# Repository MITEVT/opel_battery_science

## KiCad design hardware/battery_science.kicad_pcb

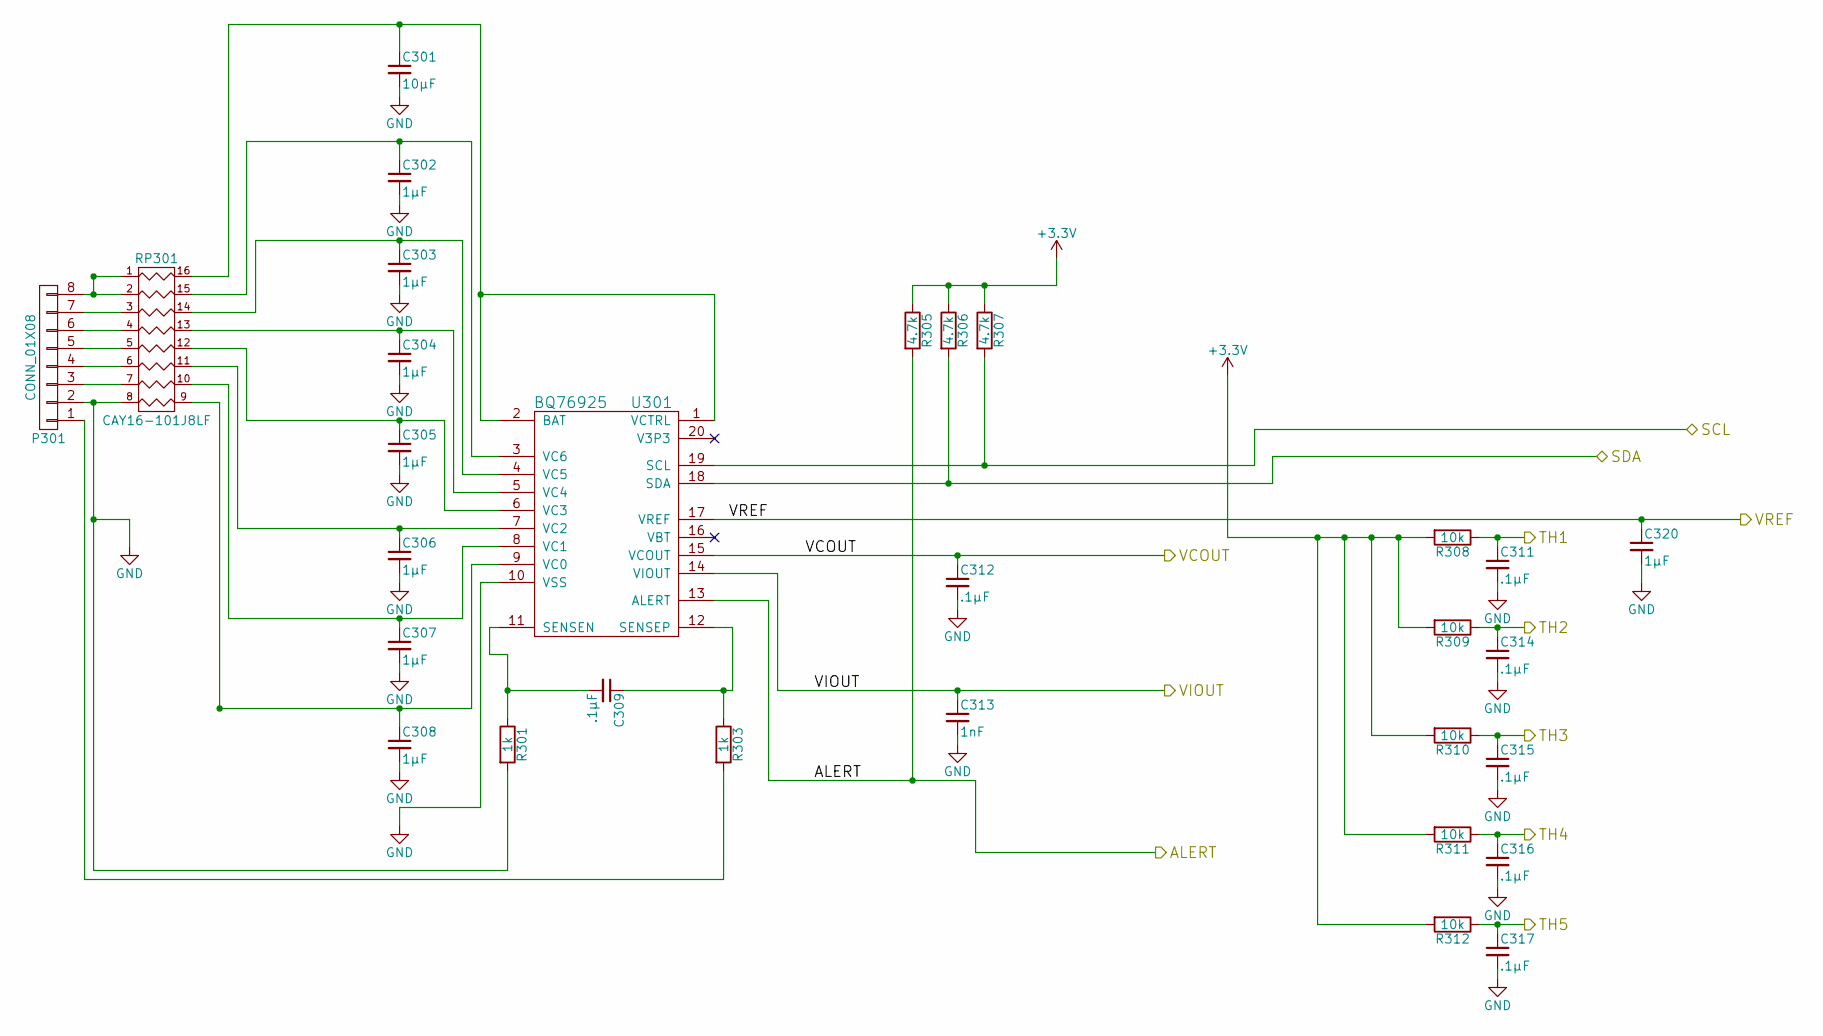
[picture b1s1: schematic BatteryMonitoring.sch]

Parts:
C301: 10μF; C_0603_HandSoldering
C302, C303, C304, C305, C306, C307, C308, C320: 1μF; C_0603_HandSoldering
C309, C311, C312, C314, C315, C316, C317: .1μF; C_0603_HandSoldering
C313: 1nF; C_0603_HandSoldering
P301: CONN_01X08; Pin_Header_Straight_1x08
R301, R303: 1k; R_0603_HandSoldering
R305, R306, R307: 4.7k; R_0603_HandSoldering
R308, R309, R310, R311, R312: 10k; R_0603_HandSoldering
RP301: CAY16-101J8LF; R_Cat16-8
U301: BQ76925; TSSOP-20_4.4x6.5mm_Pitch0.65mm

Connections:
+3V3: R305.1, R306.1, R307.1, R308.2, R309.2, R310.2, R311.2, R312.2; also elsewhere on the board
/ADC/Thermistors/TH1: C311.1, R308.1; also elsewhere on the board
/ADC/Thermistors/TH2: C314.1, R309.1; also elsewhere on the board
/ADC/Thermistors/TH3: C315.1, R310.1; also elsewhere on the board
/ADC/Thermistors/TH4: C316.1, R311.1; also elsewhere on the board
/ADC/Thermistors/TH5: C317.1, R312.1; also elsewhere on the board
/ADC/Thermistors/VCOUT: C312.1, U301.15 (VCOUT); also elsewhere on the board
/ADC/Thermistors/VIOUT: C313.1, U301.14 (VIOUT); also elsewhere on the board
/ADC/Thermistors/VREF: C320.1, U301.17 (VREF); also elsewhere on the board
/BatteryMonitoring/ALERT: R305.2, U301.13 (ALERT); also elsewhere on the board
/BatteryMonitoring/SCL: R307.2, U301.19 (SCL); also elsewhere on the board
/BatteryMonitoring/SDA: R306.2, U301.18 (SDA); also elsewhere on the board
GND: C301.2, C302.2, C303.2, C304.2, C305.2, C306.2, C307.2, C308.2, C311.2, C312.2, C313.2, C314.2, C315.2, C316.2, C317.2, C320.2, P301.2, R301.2, RP301.8, U301.10 (VSS); also elsewhere on the board
unnamed: C301.1, RP301.16 (R1), U301.1 (VCTRL), U301.2 (BAT)
unnamed: C302.1, RP301.15 (R2), U301.3 (VC6)
unnamed: C303.1, RP301.14 (R3), U301.4 (VC5)
unnamed: C304.1, RP301.13 (R4), U301.5 (VC4)
unnamed: C305.1, RP301.12 (R5), U301.6 (VC3)
unnamed: C306.1, RP301.11 (R6), U301.7 (VC2)
unnamed: C307.1, RP301.10 (R7), U301.8 (VC1)
unnamed: C308.1, RP301.9 (R8), U301.9 (VC0)
unnamed: C309.1, R303.1, U301.12 (SENSEP)
unnamed: C309.2, R301.1, U301.11 (SENSEN)
unnamed: P301.1, R303.2
unnamed: P301.3, RP301.7
unnamed: P301.4, RP301.6
unnamed: P301.5, RP301.5
unnamed: P301.6, RP301.4
unnamed: P301.7, RP301.3
unnamed: P301.8, RP301.1, RP301.2

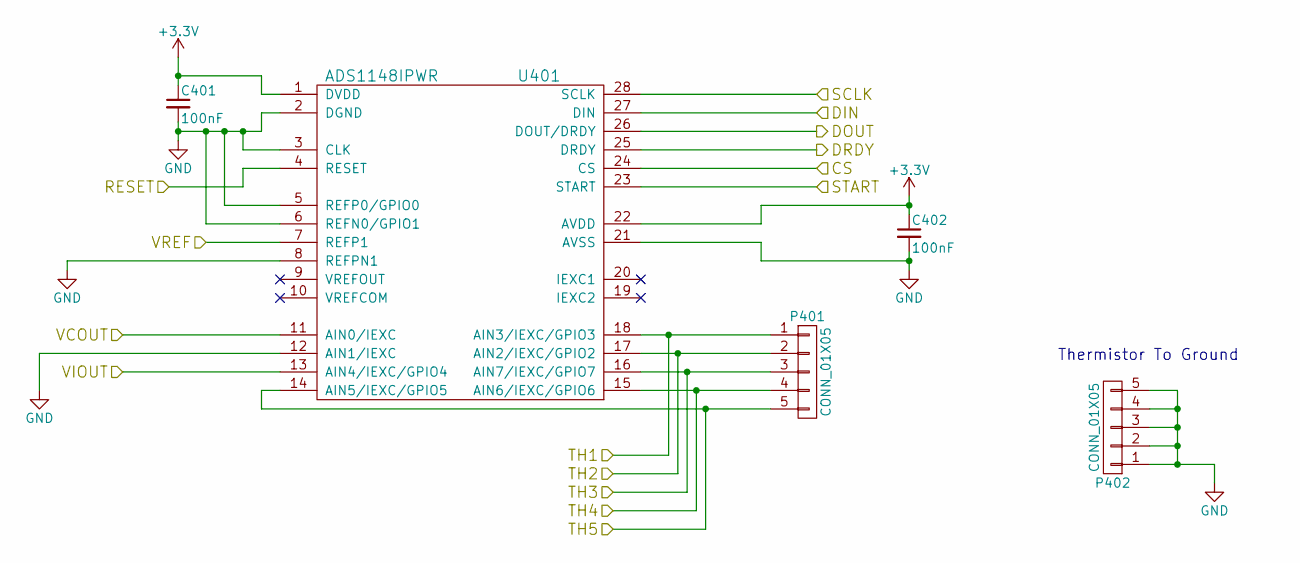
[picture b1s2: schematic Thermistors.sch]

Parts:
C401, C402: 100nF; C_0603_HandSoldering
P401, P402: CONN_01X05; Pin_Header_Straight_1x05
U401: ADS1148IPWR; TSSOP-28_4.4x9.7mm_Pitch0.65mm

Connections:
+3V3: C401.1, C402.1, U401.1 (DVDD), U401.22 (AVDD); also elsewhere on the board
/ADC/Thermistors/CS: U401.24 (CS); also elsewhere on the board
/ADC/Thermistors/DIN: U401.27 (DIN); also elsewhere on the board
/ADC/Thermistors/DOUT: U401.26 (DOUT/DRDY); also elsewhere on the board
/ADC/Thermistors/DRDY: U401.25 (DRDY); also elsewhere on the board
/ADC/Thermistors/RESET: U401.4 (RESET); also elsewhere on the board
/ADC/Thermistors/SCLK: U401.28 (SCLK); also elsewhere on the board
/ADC/Thermistors/START: U401.23 (START); also elsewhere on the board
/ADC/Thermistors/TH1: P401.1, U401.18 (AIN3/IEXC/GPIO3); also elsewhere on the board
/ADC/Thermistors/TH2: P401.2, U401.17 (AIN2/IEXC/GPIO2); also elsewhere on the board
/ADC/Thermistors/TH3: P401.3, U401.16 (AIN7/IEXC/GPIO7); also elsewhere on the board
/ADC/Thermistors/TH4: P401.4, U401.15 (AIN6/IEXC/GPIO6); also elsewhere on the board
/ADC/Thermistors/TH5: P401.5, U401.14 (AIN5/IEXC/GPIO5); also elsewhere on the board
/ADC/Thermistors/VCOUT: U401.11 (AIN0/IEXC); also elsewhere on the board
/ADC/Thermistors/VIOUT: U401.13 (AIN4/IEXC/GPIO4); also elsewhere on the board
/ADC/Thermistors/VREF: U401.7 (REFP1); also elsewhere on the board
GND: C401.2, C402.2, P402.1, P402.2, P402.3, P402.4, P402.5, U401.2 (DGND), U401.3 (CLK), U401.5 (REFP0/GPIO0), U401.6 (REFN0/GPIO1), U401.8 (REFPN1), U401.12 (AIN1/IEXC), U401.21 (AVSS); also elsewhere on the board

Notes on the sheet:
Thermistor To Ground

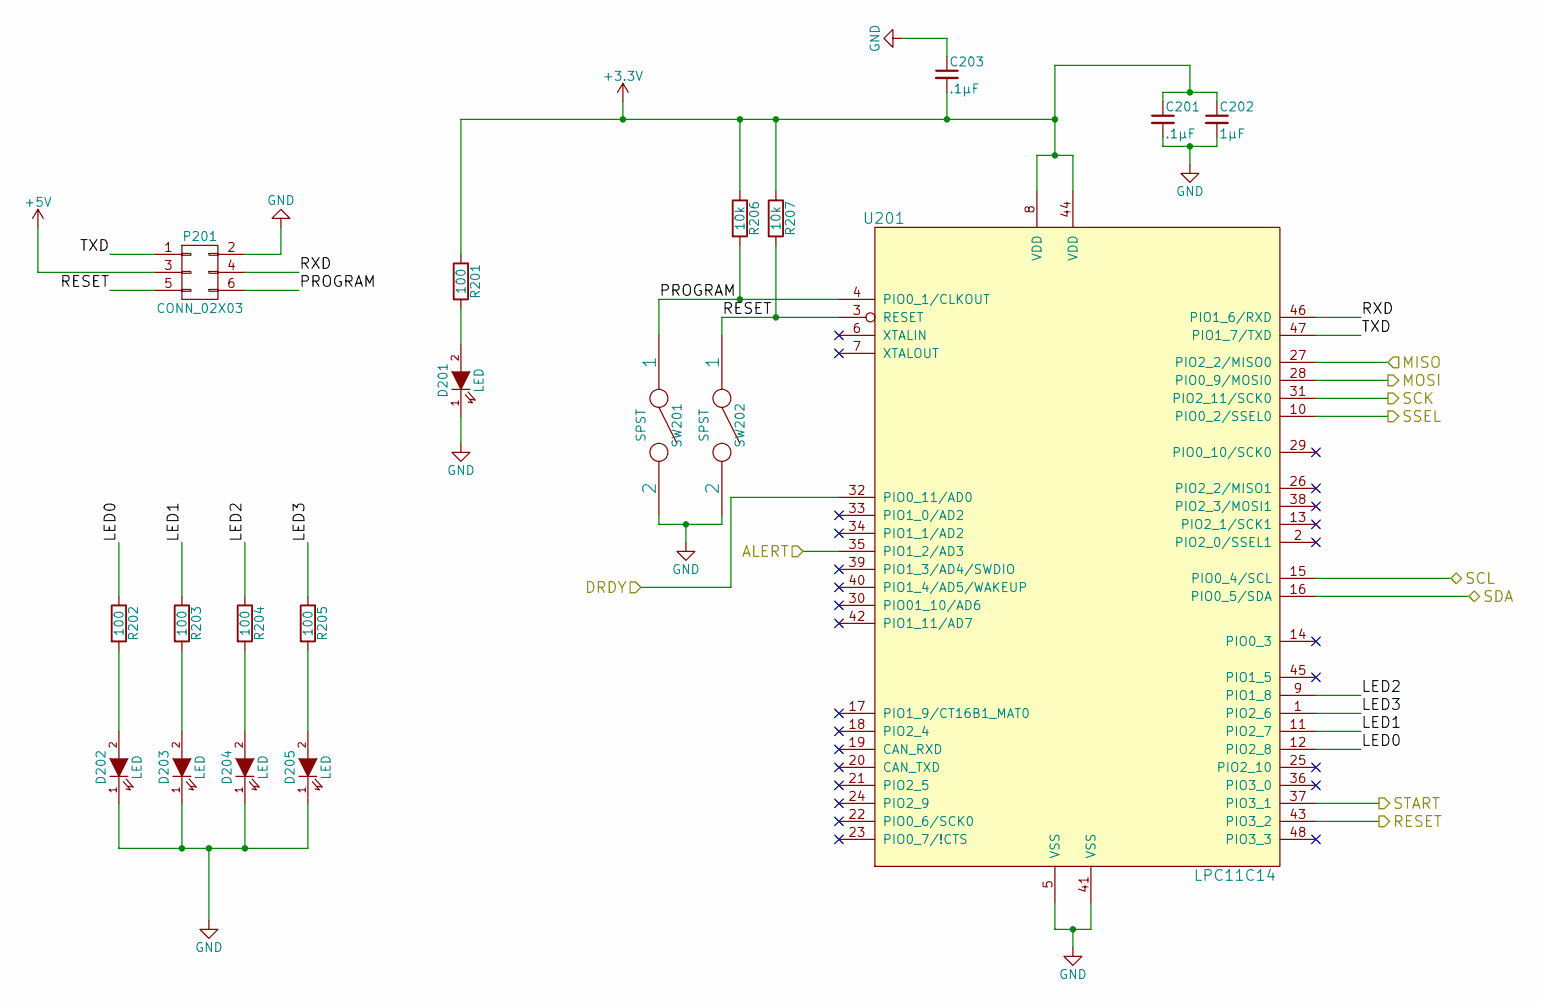
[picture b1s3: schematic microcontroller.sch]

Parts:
C201, C203: .1μF; C_0603_HandSoldering
C202: 1μF; C_0805_HandSoldering
D201, D202, D203, D204, D205: LED; LED_0805
P201: CONN_02X03; Connector_Microfit3_Header_02x03_Angled_43045-060x
R201, R202, R203, R204, R205: 100; R_0603_HandSoldering
R206, R207: 10k; R_0603_HandSoldering
SW201: SPST; SW_Micro_SPST
SW202: SPST; SW_SPST_EVPBF
U201: LPC11C14; LQFP-48_7x7mm_Pitch0.5mm

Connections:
+3V3: C201.1, C202.1, C203.2, R201.1, R206.1, R207.1, U201.8 (VDD), U201.44 (VDD); also elsewhere on the board
+5V: P201.3; also elsewhere on the board
/BatteryMonitoring/ALERT: U201.35 (PIO1_2/AD3); also elsewhere on the board
/BatteryMonitoring/SCL: U201.15 (PIO0_4/SCL); also elsewhere on the board
/BatteryMonitoring/SDA: U201.16 (PIO0_5/SDA); also elsewhere on the board
/microcontroller/DRDY: U201.32 (PIO0_11/AD0); also elsewhere on the board
/microcontroller/LED0: R202.1, U201.12 (PIO2_8)
/microcontroller/LED1: R203.1, U201.11 (PIO2_7)
/microcontroller/LED2: R204.1, U201.9 (PIO1_8)
/microcontroller/MISO: U201.27 (PIO2_2/MISO0); also elsewhere on the board
/microcontroller/MOSI: U201.28 (PIO0_9/MOSI0); also elsewhere on the board
/microcontroller/PROGRAM: P201.6, R206.2, SW201.1, U201.4 (PIO0_1/CLKOUT)
/microcontroller/RESET: P201.5, R207.2, SW202.1, U201.3 (RESET), U201.43 (PIO3_2); also elsewhere on the board
/microcontroller/RXD: P201.4, U201.46 (PIO1_6/RXD)
/microcontroller/SCK: U201.31 (PIO2_11/SCK0); also elsewhere on the board
/microcontroller/SSEL: U201.10 (PIO0_2/SSEL0); also elsewhere on the board
/microcontroller/START: U201.37 (PIO3_1); also elsewhere on the board
/microcontroller/TXD: P201.1, U201.47 (PIO1_7/TXD)
GND: C201.2, C202.2, C203.1, D201.1 (K), D202.1 (K), D203.1 (K), D204.1 (K), D205.1 (K), P201.2, SW201.2, SW202.2, U201.5 (VSS), U201.41 (VSS); also elsewhere on the board
unnamed: D201.2 (A), R201.2
unnamed: D202.2 (A), R202.2
unnamed: D203.2 (A), R203.2
unnamed: D204.2 (A), R204.2
unnamed: D205.2 (A), R205.2

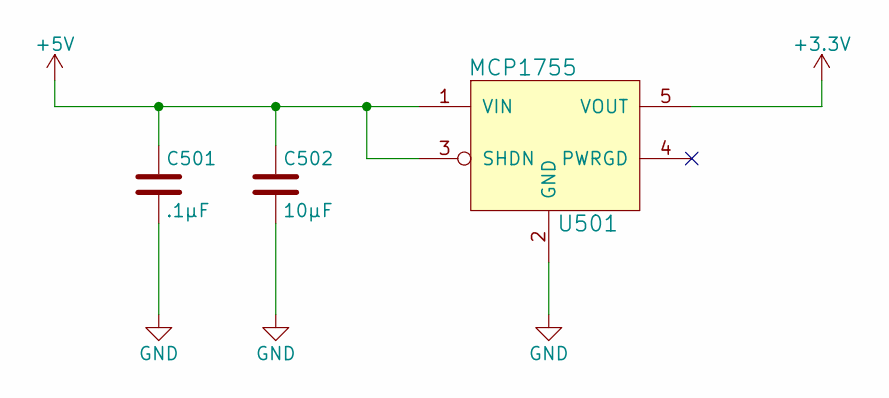
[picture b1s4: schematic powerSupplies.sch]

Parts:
C501: .1μF; C_0603_HandSoldering
C502: 10μF; C_0805_HandSoldering
U501: MCP1755

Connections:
+3V3: U501.5 (VOUT); also elsewhere on the board
+5V: C501.1, C502.1, U501.1 (VIN), U501.3 (SHDN); also elsewhere on the board
GND: C501.2, C502.2, U501.2 (GND); also elsewhere on the board

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
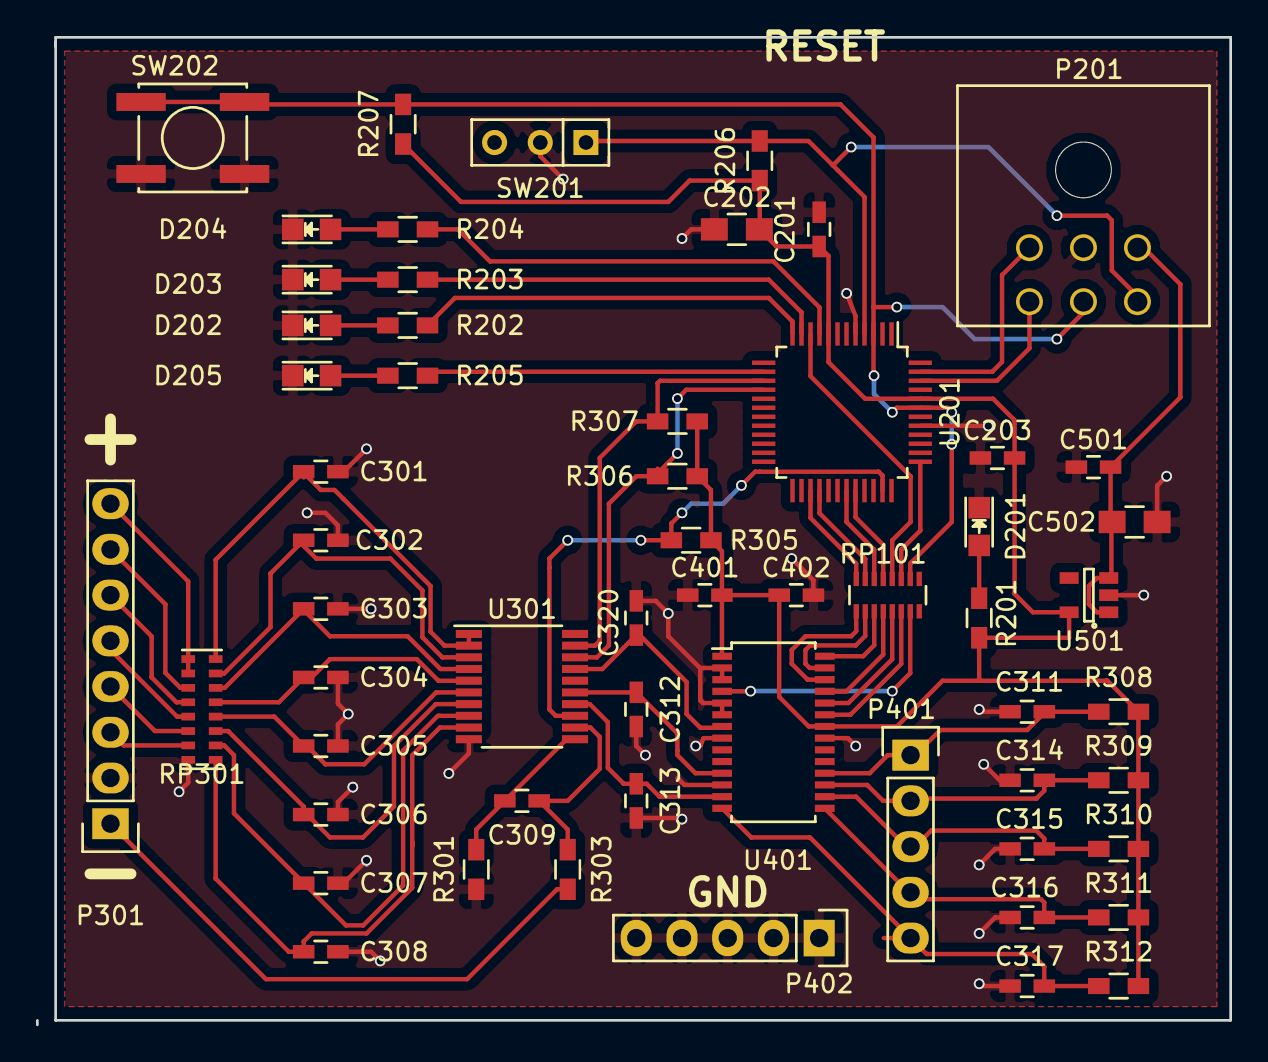
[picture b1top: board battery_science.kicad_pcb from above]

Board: 2 copper layers, 66.3 x 54.9 mm, 58 parts (0 on the bottom side), 57 nets.

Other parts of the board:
RP101: 47Ω; R_Array_Convex_8x0602

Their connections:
/ADC/Thermistors/CS: RP101.5; also elsewhere on the board
/ADC/Thermistors/DIN: RP101.2; also elsewhere on the board
/ADC/Thermistors/DOUT: RP101.1; also elsewhere on the board
/ADC/Thermistors/DRDY: RP101.4; also elsewhere on the board
/ADC/Thermistors/RESET: RP101.7; also elsewhere on the board
/ADC/Thermistors/SCLK: RP101.3; also elsewhere on the board
/ADC/Thermistors/START: RP101.6; also elsewhere on the board
/microcontroller/DRDY: RP101.13; also elsewhere on the board
/microcontroller/MISO: RP101.16; also elsewhere on the board
/microcontroller/MOSI: RP101.15; also elsewhere on the board
/microcontroller/RESET: RP101.10; also elsewhere on the board
/microcontroller/SCK: RP101.14; also elsewhere on the board
/microcontroller/SSEL: RP101.12; also elsewhere on the board
/microcontroller/START: RP101.11; also elsewhere on the board

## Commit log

2016-09-24 fun with battery science
2016-09-24 add gitignore
2016-10-06 Updated pcb layout
